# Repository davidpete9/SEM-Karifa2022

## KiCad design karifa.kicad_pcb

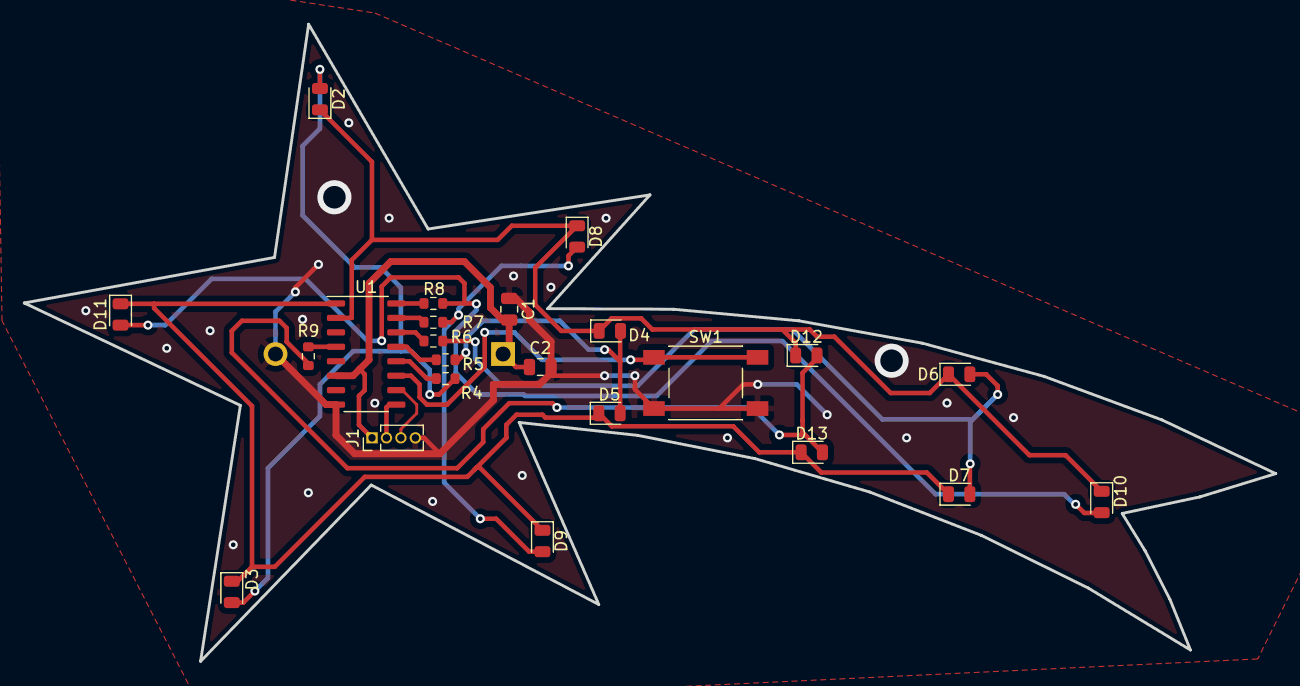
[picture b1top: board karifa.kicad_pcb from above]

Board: 2 copper layers, 110.0 x 56.0 mm, 24 parts (1 on the bottom side), 19 nets.

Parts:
BT1: Battery; CR2032_Holder
C1: 100nF; C_0805_2012Metric
C2: 10uF; C_0805_2012Metric
D2, D3, D4, D5, D6, D7, D8, D9, D10, D11, D12, D13: LED; LED_0805_2012Metric
J1: Conn_01x04; PinHeader_1x04_P1.27mm_Vertical
R4, R5, R6, R7, R8, R9: 1k; R_0603_1608Metric
SW1: SW_DPST_x2; SW_Push_K2-1102SP
U1: STC8G1K08-SOP16; STC_SOP-16_3.9x9.9mm_P1.27mm

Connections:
/MPX1: D3.1 (K), D5.1 (K), D7.1 (K), D9.1 (K), D11.1 (K), D13.1 (K), U1.1 (P1.0)
/MPX2: D2.1 (K), D4.1 (K), D6.1 (K), D8.1 (K), D10.1 (K), D12.1 (K), U1.2 (P1.1)
/P1.7: R9.2, U1.4 (P1.7)
/P3.0: J1.2, U1.9 (P3.0)
/P3.1: J1.3, U1.10 (P3.1)
/P3.3: R4.2, U1.12 (P3.3)
/P3.4: R5.2, U1.13 (P3.4)
/P3.5: R6.2, U1.14 (P3.5)
/P3.6: R7.2, U1.15 (P3.6)
/P3.7: R8.2, U1.16 (P3.7)
GND: BT1.2 (-), C1.1, C2.2, J1.4, SW1.2 (B), U1.8 (GND)
unnamed: D2.2 (A), D3.2 (A), R4.1
unnamed: D4.2 (A), D5.2 (A), R5.1
unnamed: D6.2 (A), D7.2 (A), R6.1
unnamed: D8.2 (A), D9.2 (A), R7.1
unnamed: D10.2 (A), D11.2 (A), R8.1
unnamed: D12.2 (A), D13.2 (A), R9.1
unnamed: SW1.1 (A), U1.11 (P3.2)
VCC: BT1.1 (+), C1.2, C2.1, J1.1, U1.6 (VCC)

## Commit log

2022-10-06 Schematic
2022-10-10 proto nyak
2022-10-18 karifa outline
2022-10-22 nyakterv majdnem kesz
2022-10-22 nyakterv haladas
2022-10-25 nyakterv kesz
2022-10-25 szimbolumok, footprintek
2022-10-25 panelizacio
2022-10-26 kisebb javitasok
2022-10-26 hullocsillag
2022-10-27 javitasok
2022-10-27 BOM, gerber, gyartasra adott valtozat
2022-10-30 javitas
2022-10-30 Fixed some stuff in repo + additional tab so that the guys at JLCPCB will be happy.
2022-10-30 Sent to fab.
2022-11-03 Moved hardware design files to a separate directory.
2022-11-03 Added source files from previous project.
2022-11-03 Works on the prototype hardware.
2022-11-04 Added RGB LED driver.
2022-11-13 Ported the retro animation to this revision.
2022-11-14 Works on real hardware.
2022-11-15 Animations work in progress.
2022-11-16 Changed animation engine.
2022-11-18 Battery level indication at startup.
2022-11-19 Fixed-point arithmetic for battery level calculation.
2022-11-19 Bugfix.
2022-11-19 Animation engine rewrite.
2022-12-04 Turns off after 5 hours.
2022-12-04 Final animations for karifa.
2022-12-06 Finalized hullocsillag animations.
2022-12-06 Fixed battery level indicator on hullocsillag.
2023-10-23 Updated BOM for this year.
2023-10-30 Added initial PY32-based firmware.
2023-10-30 Small cleanup.
2023-10-31 Correctly drives the RGB LED.
